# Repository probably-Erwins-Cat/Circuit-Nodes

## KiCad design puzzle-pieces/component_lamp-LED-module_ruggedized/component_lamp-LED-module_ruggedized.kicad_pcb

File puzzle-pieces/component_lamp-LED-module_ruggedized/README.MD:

# Lamp (ruggedized LED)

A lamp is the ideal starting component for electronics. Unfortunately, the tiny E10 lamps and sockets are oftentimes of questionable quality. A ruggedized LED can be used as alternative to a lamp.

# Usage

A reverse mounted large LED in the inside with protection, over-voltage diodes and reasonably large resistor in series can act as a lamp replacement in terms of functionality. LEDs have much longer life than typical E10 lamps, so you can expect that these ruggedized LED lamps will last for ages.

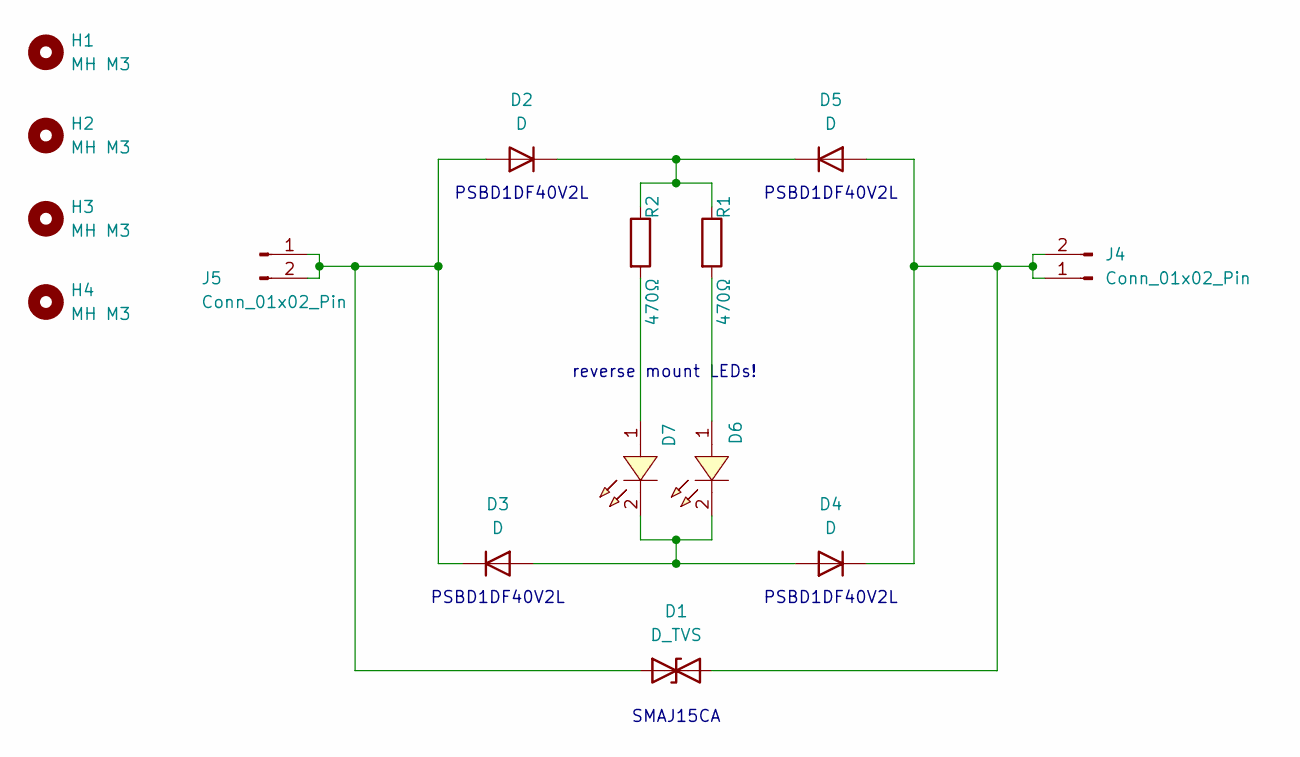
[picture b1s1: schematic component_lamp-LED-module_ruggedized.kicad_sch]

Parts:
D1: D_TVS; D_SMA_Handsoldering; LCSC C2848698
D2, D3, D4, D5: D; SOD-123FL_L2.8-W1.8-LS3.8-RD; LCSC C496544
D6, D7: XL-6028UGC-FB; LED-SMD_L3.2-W2.8-LS5.9_GT-6028W-1023; LCSC Part C3646964
H1, H2, H3, H4: MH M3; MountingHole_3.0mm_M3_tight
J4, J5: Conn_01x02_Pin; Magnetic_Connector_1x02_P2.5mm_Horizontal_round-ears
R1, R2: 470Ω; R_1206_3216Metric_Pad1.30x1.75mm_HandSolder

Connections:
unnamed: D1.1 (A1), D2.2 (A), D3.1 (K), J5.1, J5.2
unnamed: D1.2 (A2), D4.1 (K), D5.2 (A), J4.1, J4.2
unnamed: D2.1 (K), D5.1 (K), R1.1, R2.1
unnamed: D3.2 (A), D4.2 (A), D6.2, D7.2
unnamed: D6.1, R1.2
unnamed: D7.1, R2.2

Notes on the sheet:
PSBD1DF40V2L
SMAJ15CA
reverse mount LEDs!

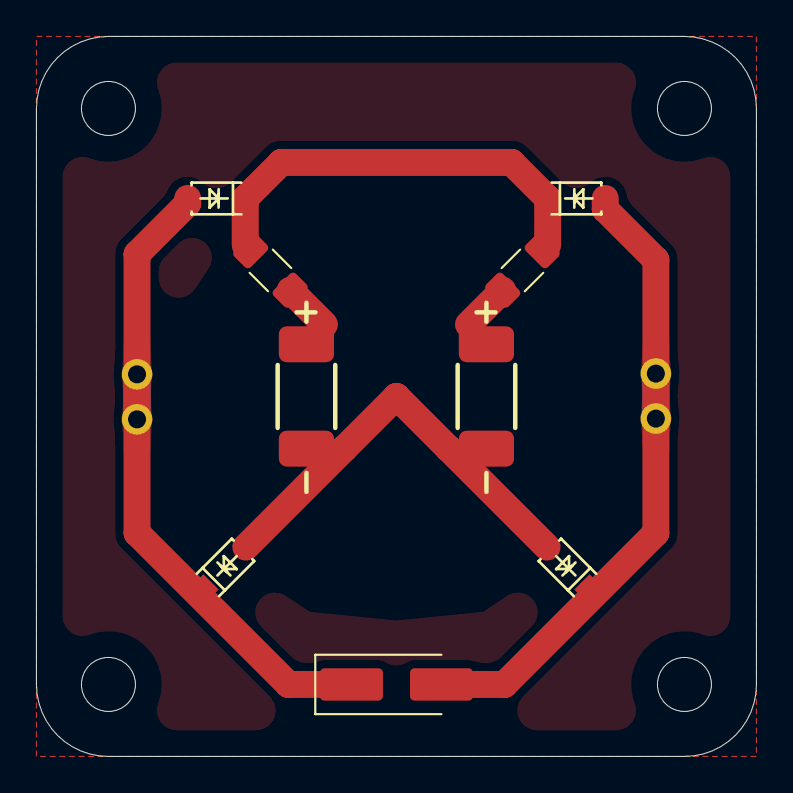
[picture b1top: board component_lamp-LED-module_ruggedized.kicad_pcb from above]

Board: 2 copper layers, 40.0 x 40.0 mm, 15 parts (0 on the bottom side), 6 nets.

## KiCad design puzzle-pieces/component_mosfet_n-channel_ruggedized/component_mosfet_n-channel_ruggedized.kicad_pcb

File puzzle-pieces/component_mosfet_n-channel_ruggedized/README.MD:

# N-channel MOSFET (ruggedized)

An N‑channel MOSFET is a semiconductor switch controlled by a gate voltage. It is widely used for efficient switching of currents in low-side configurations and is an excellent device to introduce switching concepts in class.

## Functional description
The device has three terminals:

| Terminal | Function |
|---|---|
| Drain (D) | Current enters |
| Source (S) | Current exits |
| Gate (G) | Voltage that controls conduction |

- Gate low (near 0 V): MOSFET is OFF (blocks current).  
- Gate high (above threshold): MOSFET turns ON and allows current from drain to source.

## How It Works

This switch acts as a **low-side transistor driver**:

- **S (Source):** Connect to the system ground.  
- **D (Drain):** Connect to the load’s return. Load positive should be from your power source (e.g., 5–20 V).  
- **G (Control):** Logic control input (e.g., MCU GPIO, pushbutton output).

## Protection built in

- **Gate protection:**  
  - 5.1 V zener from Gate → Source clamps excessive positive gate voltage.  
  - 1N4148 diode from Source → Gate clamps negative gate swings.  
  - 220 Ω series resistor slows transient injection into the gate.  
  - 100 kΩ pulldown to ground keeps the MOSFET off when control is floating.

- **Drain-Source clamp:**  
  - 24 V zener across Drain → Source absorbs spikes or wrong wiring stress.  
  - Upstream resettable fuse limits energy under sustained fault.

This combination allows the MOSFET to survive common wiring mistakes (e.g., swapping control/GND/VIN) without immediate failure.

## Parts List (BOM)

| Ref     | Function                         | Value / Part                     |
|---------|----------------------------------|----------------------------------|
| Q1      | Main N-MOSFET                    | NDT3055L (SOT-223)               |
| R1      | Gate series resistor             | 220 Ω, 1206                      |
| R2      | Gate pulldown                    | 100 kΩ, 1206                     |
| D_GS_Z  | Gate positive zener              | 5.1 V, SOD-123                   |
| D_GS_D  | Gate negative clamp              | 1N4148W, SOD-123                 |
| D_DS_Z  | Drain-Source clamp (rugged)      | 24 V zener, SMA (1 W)            |

Substitute any logic-level part with:
- **V<sub>DS</sub> ≥ 30 V**
- Low **R<sub>DS(on)</sub> @ V<sub>GS</sub> ≤ 5 V**
- Same pinout (G/D/S)

## Limitations & Safety

- This piece is designed for educational demonstrations with reasonable current loads (≤ a few amps).  
- Gate protection will **not** protect against arbitrarily high voltages or sustained fault currents without an upstream fuse.  
- Always provide proper upstream overcurrent protection (PTC / fuse) when using this in student circuits.

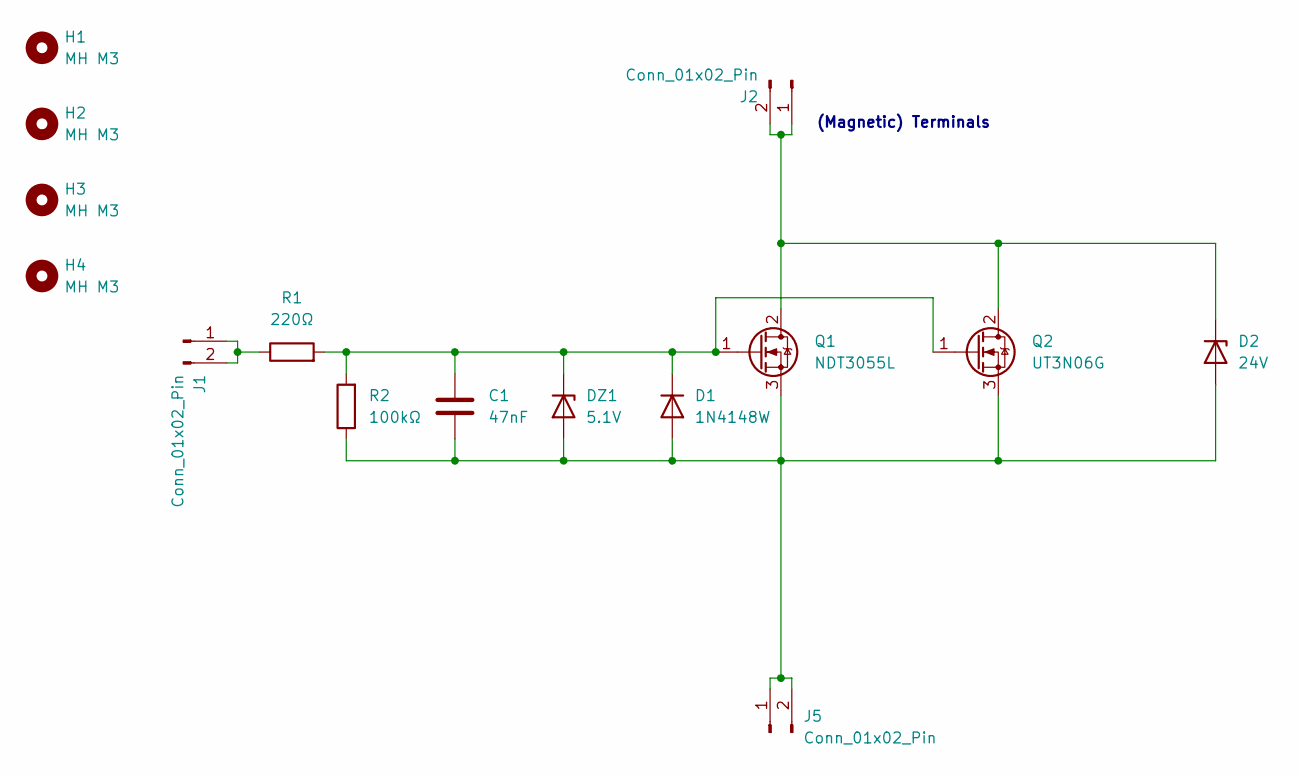
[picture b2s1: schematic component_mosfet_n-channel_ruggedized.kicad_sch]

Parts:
C1: 47nF; C_1206_3216Metric_Pad1.33x1.80mm_HandSolder; LCSC C303962
D1: 1N4148W; Nexperia_CFP3_SOD-123W; LCSC C81598
D2: 24V; D_SMA; LCSC C155317
DZ1: 5.1V; Nexperia_CFP3_SOD-123W; LCSC C2827905
H1, H2, H3, H4: MH M3; MountingHole_3.0mm_M3_tight
J1, J2, J5: Conn_01x02_Pin; Magnetic_Connector_1x02_P2.5mm_Horizontal_round-ears
Q1: NDT3055L; SOT-223-3_TabPin2; LCSC C5354979
Q2: UT3N06G; SOT-89-3_Handsoldering; LCSC C127044
R1: 220Ω; R_1206_3216Metric_Pad1.30x1.75mm_HandSolder; LCSC C17957
R2: 100kΩ; R_1206_3216Metric_Pad1.30x1.75mm_HandSolder; LCSC C17900

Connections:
unnamed: C1.2, D1.2 (A), D2.2 (A), DZ1.2 (A), J5.1, J5.2, Q1.3 (S), Q2.3 (S), R2.1
unnamed: C1.1, D1.1 (K), DZ1.1 (K), Q1.1 (G), Q2.1 (G), R1.2, R2.2
unnamed: D2.1 (K), J2.1, J2.2, Q1.2 (D), Q2.2 (D)
unnamed: J1.1, J1.2, R1.1

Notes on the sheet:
(Magnetic) Terminals

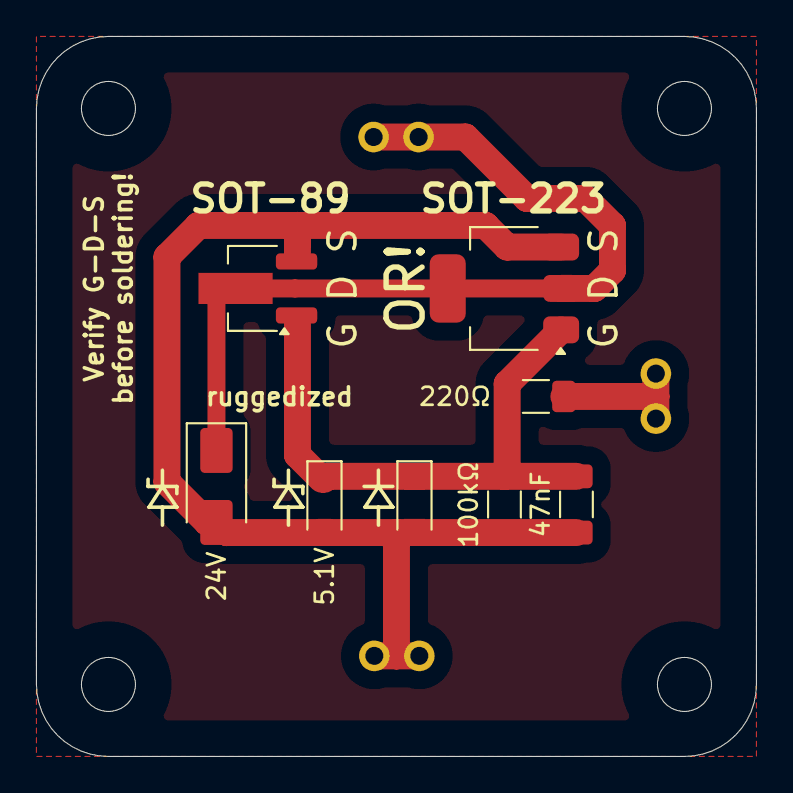
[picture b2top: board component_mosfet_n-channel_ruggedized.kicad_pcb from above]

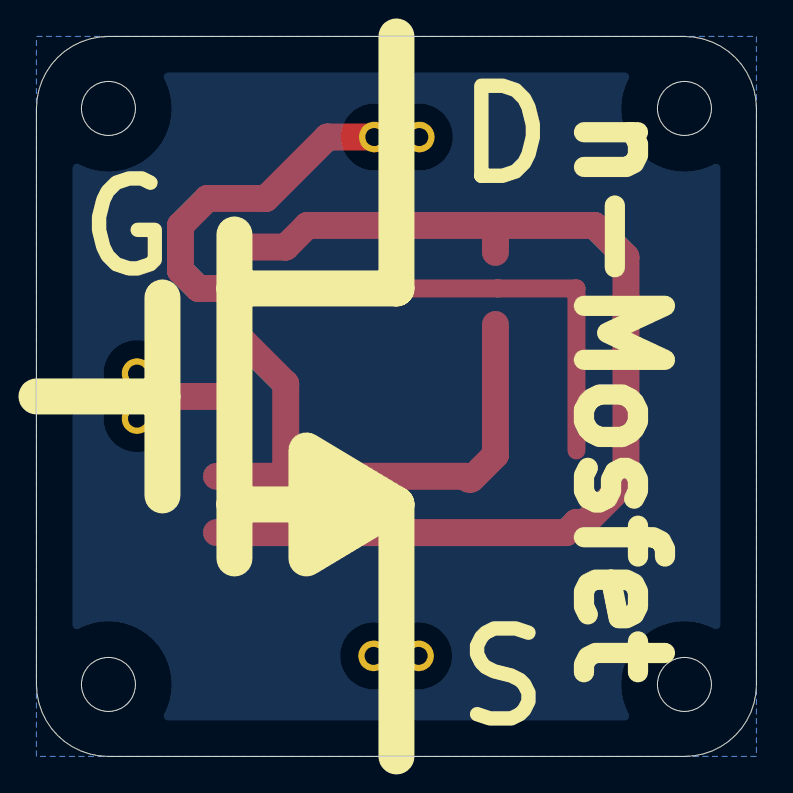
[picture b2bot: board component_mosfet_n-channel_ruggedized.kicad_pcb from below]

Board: 2 copper layers, 40.0 x 40.0 mm, 15 parts (4 on the bottom side), 4 nets.

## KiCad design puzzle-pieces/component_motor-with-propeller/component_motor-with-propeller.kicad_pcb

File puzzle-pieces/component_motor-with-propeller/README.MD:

# Motor with Propeller

Like a lamp, a DC motor is a illustrative component of transforming electricity in a different energy form. Here, a simple motor with 24mm base and shaft for propeller mount is used, found in various entry level electronics kits. Many DC motors run in opposite direction, when polarity is switched, and others have reverse polarity switch and can only run in one directiong (like AC motors).

## Mounting

The 3D printable mount for motor comes with three slots for heat inserts.

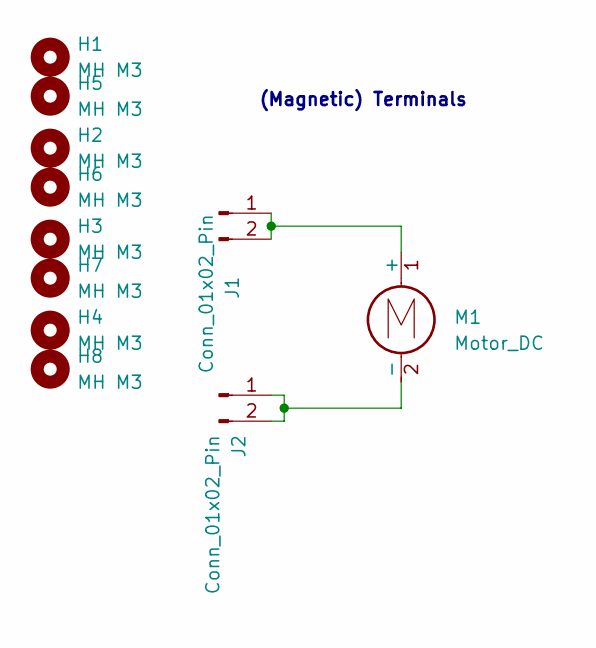
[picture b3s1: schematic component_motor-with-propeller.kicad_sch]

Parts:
H1, H2, H3, H4, H5, H6, H7, H8: MH M3; MountingHole_3.0mm_M3_tight
J1, J2: Conn_01x02_Pin; Magentic_Connector_1x02_P2.5mm_Horizontal
M1: Motor_DC; motor-with-propeller

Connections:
unnamed: J1.1, J1.2, M1.1 (+)
unnamed: J2.1, J2.2, M1.2 (-)

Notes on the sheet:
(Magnetic) Terminals

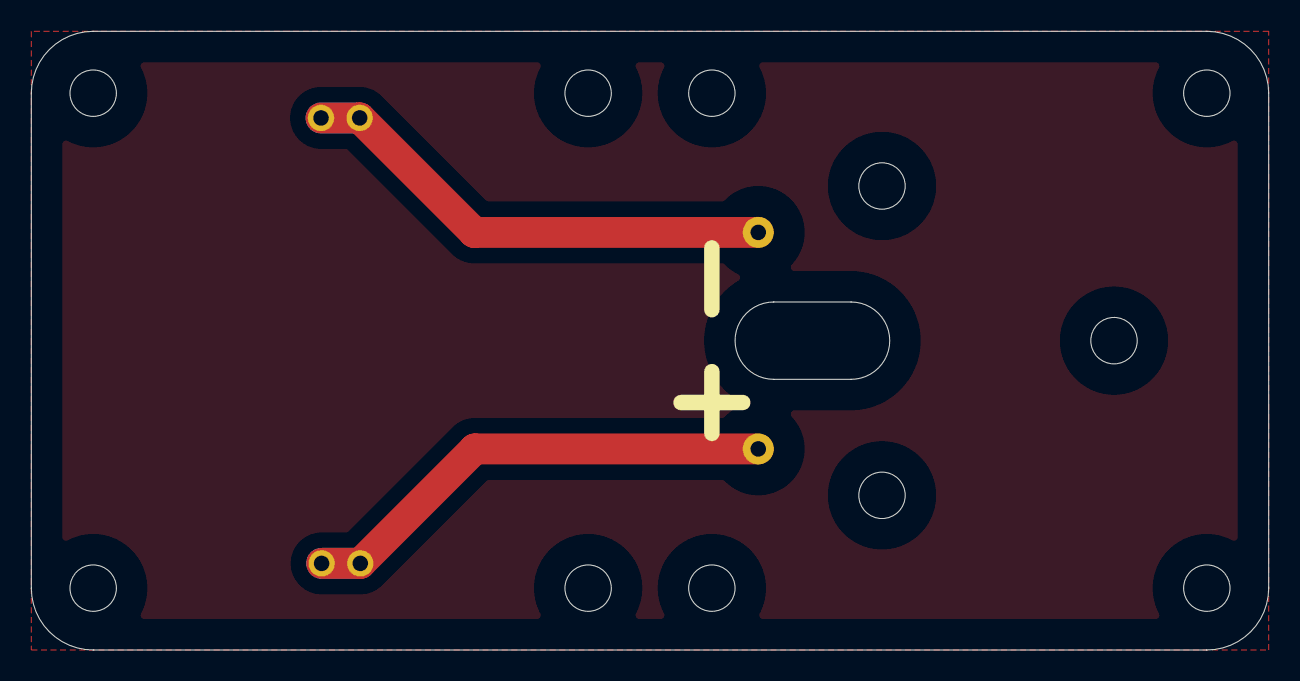
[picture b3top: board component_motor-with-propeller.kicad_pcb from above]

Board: 2 copper layers, 80.0 x 40.0 mm, 11 parts (1 on the bottom side), 2 nets.

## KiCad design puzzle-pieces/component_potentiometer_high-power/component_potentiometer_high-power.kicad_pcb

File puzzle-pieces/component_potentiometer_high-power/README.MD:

# Potentiometer — High Power

A  potentiometer is a mechanical variable resistor with a rotating shaft that changes the resistance between terminals. It is commonly used as a user-adjustable voltage divider (e.g., volume, brightness, or level controls) and for fine manual adjustments in experiments and demo circuits. 

*This is the rotary high power potentiometer version with bottom-side mounting for illustrating the schematic symbol.*

## Basic description

A potentiometer usually has three terminals: two fixed end terminals and one wiper (middle terminal). When used as a variable voltage divider the wiper provides an adjustable output between the two end terminals. When one end terminal is left disconnected the potentiometer acts as a variable resistor between the wiper and the remaining end.

## Typical uses in circuits
- User-adjustable voltage divider (volume, brightness, contrast)
- Manual offset or trim control in simple analog circuits
- Teaching component for demonstrating potentiometers and voltage division

## Wiring, Fixating and formulas
- Voltage divider when wired between `V_in` and `GND` with the wiper as output `V_out`:

	\[V_{out} = V_{in} \cdot \frac{R_{w}}{R_{total}}\]

	where `R_w` is the resistance from the wiper to ground and `R_total` is the total potentiometer resistance.

- As a variable resistor (rheostat) connect one end and the wiper; the resistance between them changes with the slider position.
- M2 screws for fixating the potentiometers should be secured and of correct length. Thread depth is approx 2mm, so 4mm M2 screws will usually fit. Take care of the correct applied torque to not strip the screws.
- *The potentiometers are quite tall*. **A printable base with large cut-out in the center should be used.**

## Why High Power Potentiometer
Usual potentiometers can only dissipate a few tens of milli Watts. This can dissipate 1-2 W, depending on model. This allows a few more use cases of voltage and power regulation than smaller potentiometers without introducing more complex parts for voltage and power regulation (mosfets, etc.) to the students.

Further, high power potentiometers are often available with lower resistance ratings, making them viable for circuits that require lower resistances. Standard potentiometers are usually 10k or 100k Ohms.

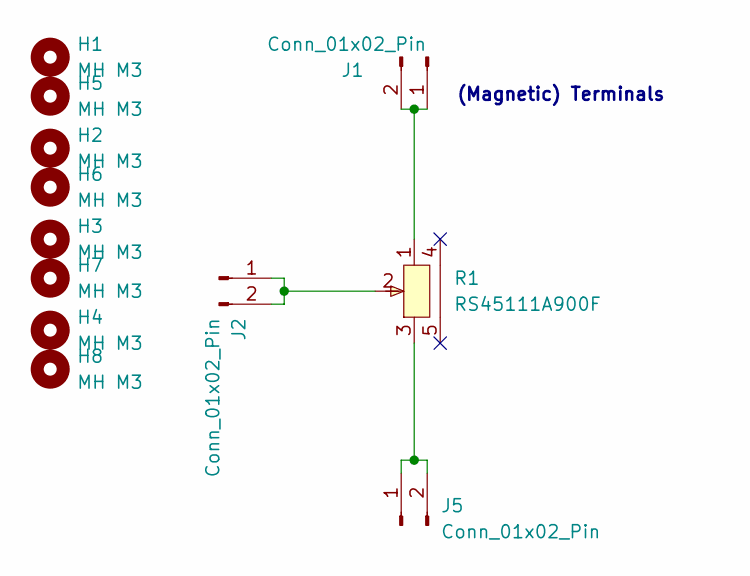
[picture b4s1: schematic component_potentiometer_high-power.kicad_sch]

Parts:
H1, H2, H3, H4, H5, H6, H7, H8: MH M3; MountingHole_3.0mm_M3_tight
J1, J2, J5: Conn_01x02_Pin; Magentic_Connector_1x02_P2.5mm_Horizontal
R1: RS45111A900F; RES-ADJ-THT-High-Power-Conrad; LCSC Part C370991

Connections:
unnamed: J1.1, J1.2, R1.1
unnamed: J2.1, J2.2, R1.2
unnamed: J5.1, J5.2, R1.3

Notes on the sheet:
(Magnetic) Terminals

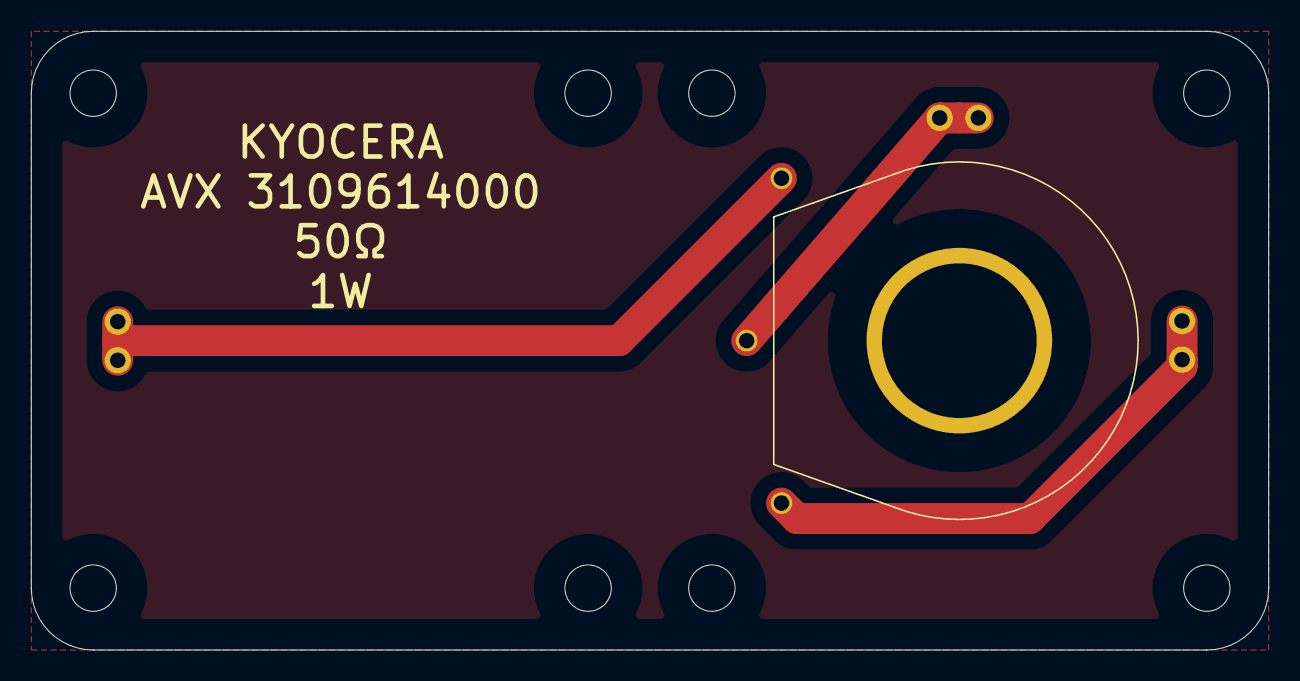
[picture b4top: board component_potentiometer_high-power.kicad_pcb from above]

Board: 2 copper layers, 80.0 x 40.0 mm, 12 parts (1 on the bottom side), 3 nets.

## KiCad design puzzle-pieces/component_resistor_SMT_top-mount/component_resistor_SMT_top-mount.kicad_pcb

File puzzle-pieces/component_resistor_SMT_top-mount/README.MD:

# Resistor (SMT)

An SMT resistor is a compact passive component used to set currents and voltages in circuits. For school-level explanations we use Ohm’s law:

\[U = I \cdot R\]

where $U$ is voltage (V), $I$ is current (A) and $R$ is resistance (Ω).

## Typical uses in circuits
- Current limiting (e.g., protecting LEDs).
- Voltage dividers for simple references.
- Basic signal conditioning in combination with capacitors or inductors.

## Practical and safety notes
- Power dissipation: resistors convert electrical energy to heat. Use the formula
  \[P = U \cdot I = I^2 \cdot R = \dfrac{U^2}{R}.\]
  Choose resistor power ratings appropriate for expected dissipation; in low-voltage classroom experiments this is often not critical but remains good practice.

## E-series (preferred values)
- Resistors are manufactured in preferred-value E-series (for example E12 or E24). These series explain the commonly available standard values (10, 12, 15, 18, 22, 27, 33, … etc.). Use the E-series as a teaching point for availability of component values.

## Classroom kit recommendations
- Keep a range from a few ohms up to 1 MΩ to support different experiments; include standard values such as 100 Ω, 330 Ω, 1 kΩ, 10 kΩ, and 100 kΩ.

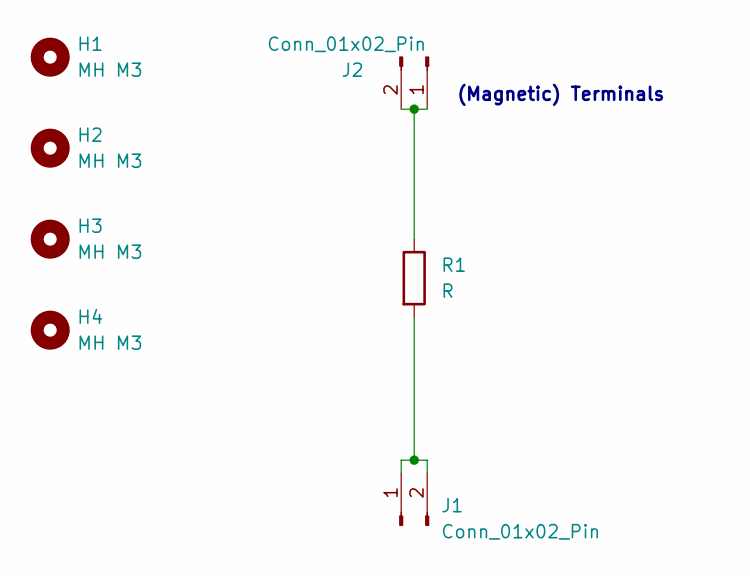
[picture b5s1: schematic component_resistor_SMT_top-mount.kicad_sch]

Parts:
H1, H2, H3, H4: MH M3; MountingHole_3.0mm_M3_tight
J1, J2: Conn_01x02_Pin; Magentic_Connector_1x02_P2.5mm_Horizontal
R1: R; R_2512_6332Metric_Pad1.40x3.35mm_HandSolder

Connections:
unnamed: J1.1, J1.2, R1.2
unnamed: J2.1, J2.2, R1.1

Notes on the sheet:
(Magnetic) Terminals

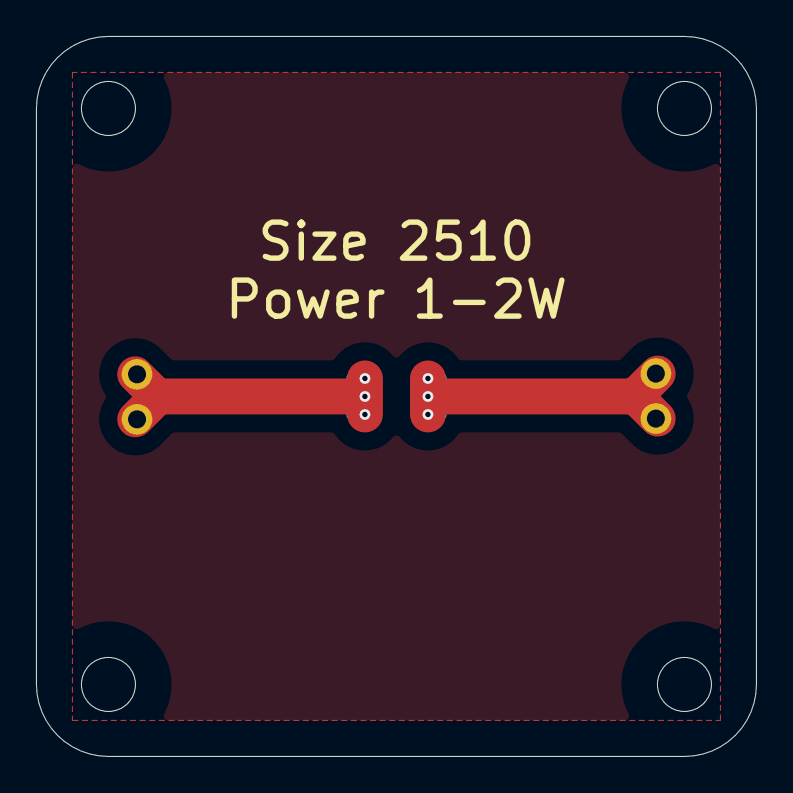
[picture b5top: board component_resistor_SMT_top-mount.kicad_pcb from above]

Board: 2 copper layers, 40.0 x 40.0 mm, 7 parts (1 on the bottom side), 2 nets.
